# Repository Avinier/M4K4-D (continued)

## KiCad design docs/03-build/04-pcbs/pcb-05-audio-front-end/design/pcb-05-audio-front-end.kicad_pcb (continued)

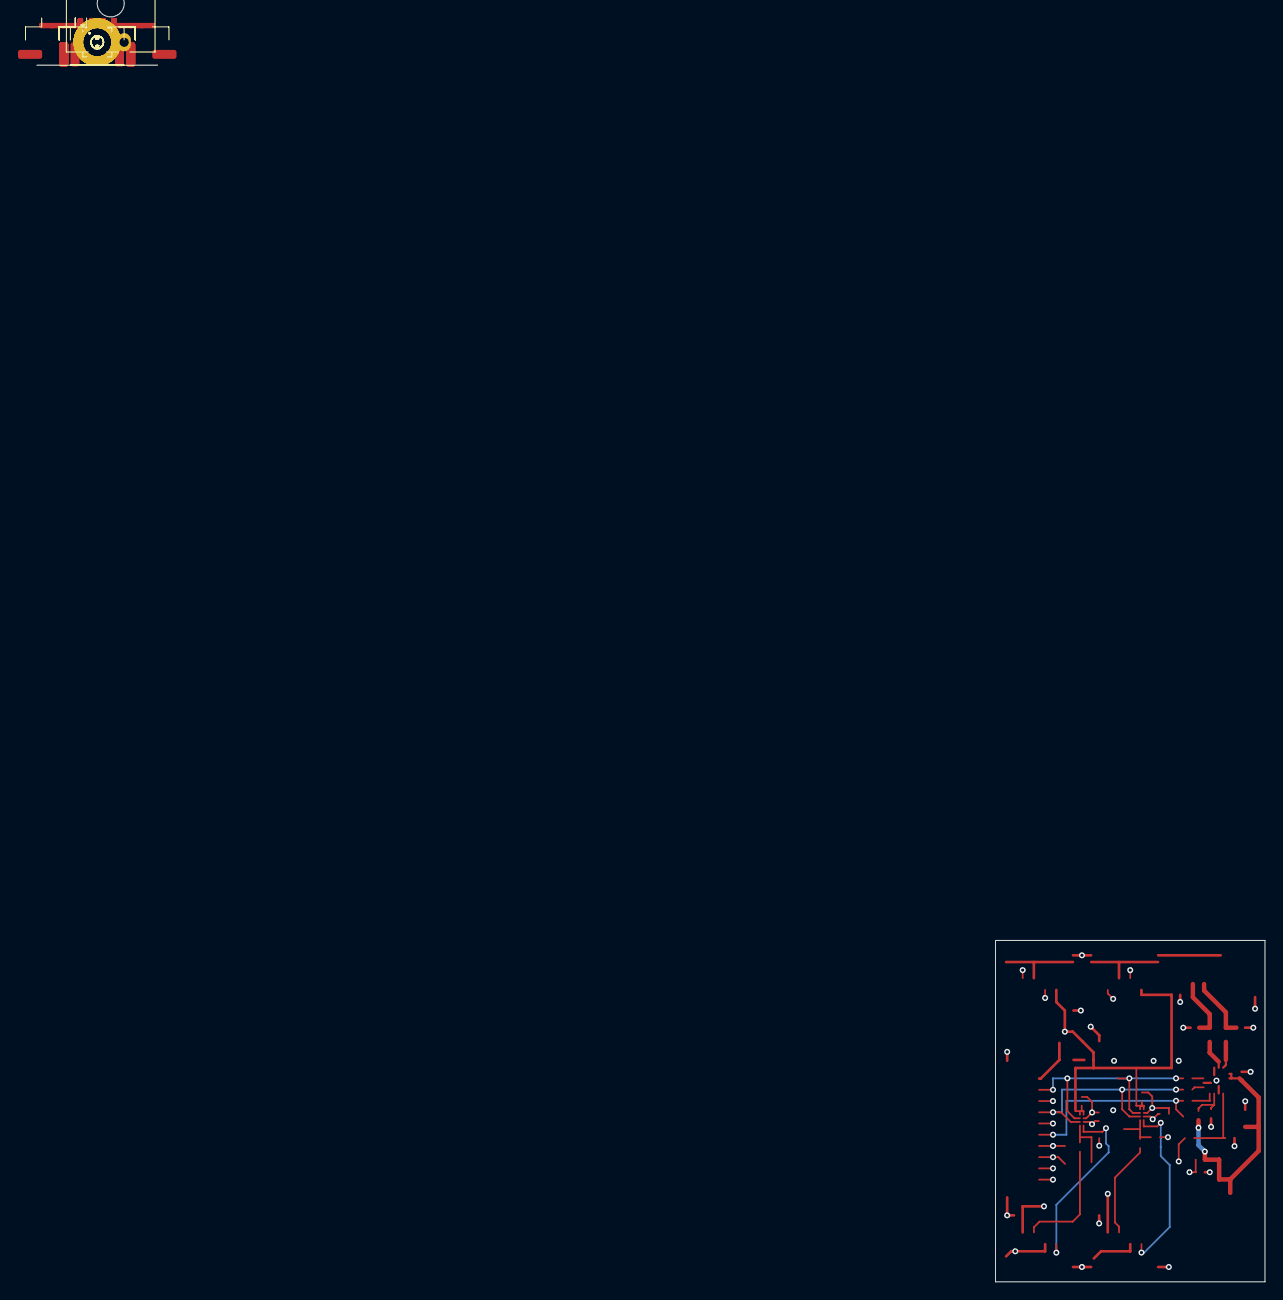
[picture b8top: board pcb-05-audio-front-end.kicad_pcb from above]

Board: 4 copper layers, 30.0 x 38.0 mm, 55 parts (0 on the bottom side), 29 nets.

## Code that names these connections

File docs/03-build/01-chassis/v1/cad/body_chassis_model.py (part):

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C0_LINK_ADAPTER_TOP_PLUGS = (36.0, 54.0, 29.0, 42.0, 112.0, 116.0)
C0_LINK_ADAPTER_SIDE_PLUG = (26.0, 38.0, 45.0, 54.0, 108.0, 112.5)
# C3 carrier (PCB-10, RP-02 CCD-HDL-03: DevKitC backplane with the base-link
# THVD1451, the TPS3436 window watchdog, READY logic, the 74LVC1G08 driver sleep gate; DRV8833 mapping in 04-pcbs/power-boards.md sec 2.4 (D-038),
# driver/sensor connectors and test points). Nothing modelled it, and the bare
# DevKitC floated over PCB-04 with its header pins in PCB-04's parts envelope.
# A free-volume scan found one home: standing vertical on the -Y side wall
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    ("J10-2", "GH", 6, "base link RS-422 to PCB-09 J9-2"),
    ("J10-3", "GH", 4, "encoder L"),
    ("J10-4", "GH", 4, "encoder R"),
    ("J10-5", "GH", 6, "left DRV8833: SLP (AND of GPIO21 and BASE_READY), IN1, IN2, FLT (wired-OR GPIO9), GND, spare (D-038)"),
    ("J10-6", "GH", 6, "right DRV8833: SLP (AND of GPIO21 and BASE_READY), IN1, IN2, FLT (wired-OR GPIO9), GND, spare (D-038)"),
    ("J10-7", "GH", 8, "IMU PCB-07 (SPI)"),
    ("J10-8", "GH", 5, "nose pod, one cable (D-013): +5V and Vo for the GP2Y0A21YK0F, GND, +3V3 and OUT for the DRV5055 Hall board"),
    ("J10-10", "GH", 4, "rear TCRT cartridge"),
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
